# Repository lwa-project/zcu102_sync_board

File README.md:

ZCU102 Sync Board
=================

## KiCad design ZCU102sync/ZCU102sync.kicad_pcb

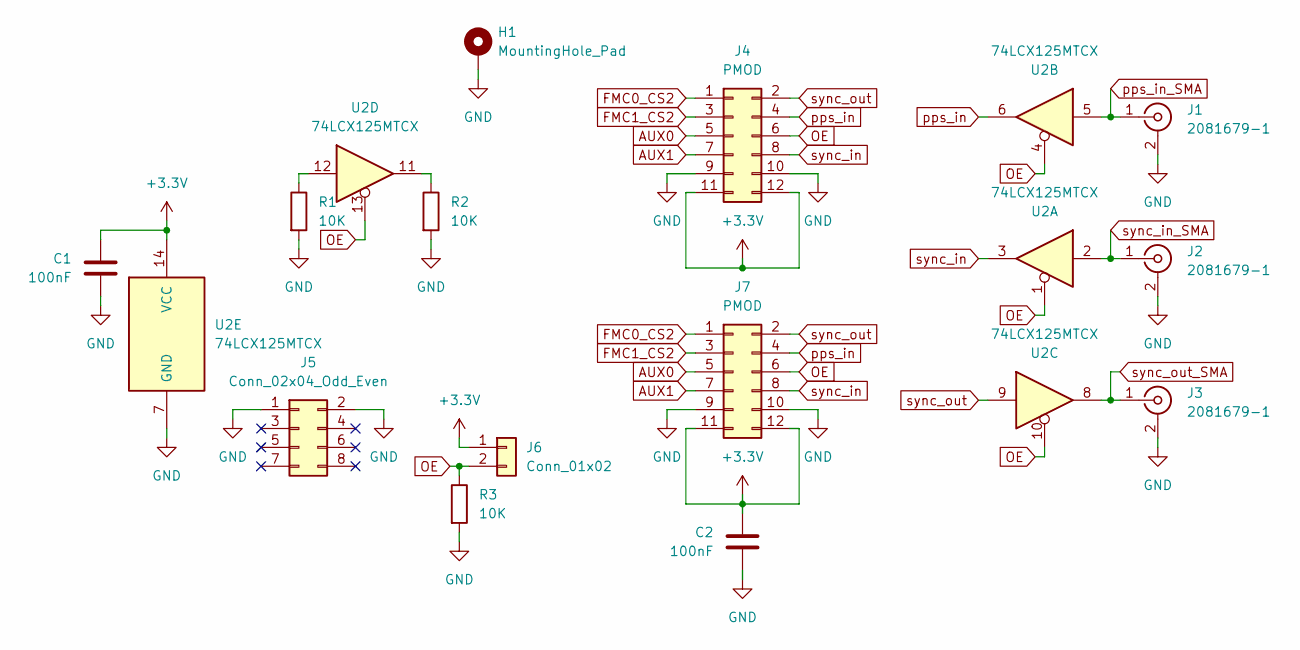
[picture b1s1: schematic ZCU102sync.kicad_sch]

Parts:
C1, C2: 100nF; C_1206_3216Metric_Pad1.33x1.80mm_HandSolder
H1: MountingHole_Pad; MountingHole_3.5mm_Pad_Via
J1, J2, J3: 2081679-1; SMA_Amphenol_132203-12_Horizontal
J4: PMOD; PinSocket_2x06_P2.54mm_Vertical
J5: Conn_02x04_Odd_Even; PinSocket_2x04_P2.54mm_Vertical
J6: Conn_01x02; PinHeader_2x01_P2.54mm_Vertical
J7: PMOD; PinHeader_2x06_P2.54mm_Vertical
R1, R2, R3: 10K; R_1206_3216Metric_Pad1.30x1.75mm_HandSolder
U2: 74LCX125MTCX; TSSOP-14_4.4x5mm_P0.65mm

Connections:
+3.3V: C1.1, C2.1, J4.11, J4.12, J6.1, J7.11, J7.12, U2.14 (VCC)
AUX0: J4.5, J7.5
AUX1: J4.7, J7.7
FMC0_CS2: J4.1, J7.1
FMC1_CS2: J4.3, J7.3
GND: C1.2, C2.2, H1.1, J1.2 (Ext), J2.2 (Ext), J3.2 (Ext), J4.9, J4.10, J5.1, J5.2, J7.9, J7.10, R1.2, R2.2, R3.2, U2.7 (GND)
unnamed: R1.1, U2.12
unnamed: R2.1, U2.11
OE: J4.6, J6.2, J7.6, R3.1, U2.1, U2.4, U2.10, U2.13
pps_in: J4.4, J7.4, U2.6
pps_in_SMA: J1.1 (In), U2.5
sync_in: J4.8, J7.8, U2.3
sync_in_SMA: J2.1 (In), U2.2
sync_out: J4.2, J7.2, U2.9
sync_out_SMA: J3.1 (In), U2.8

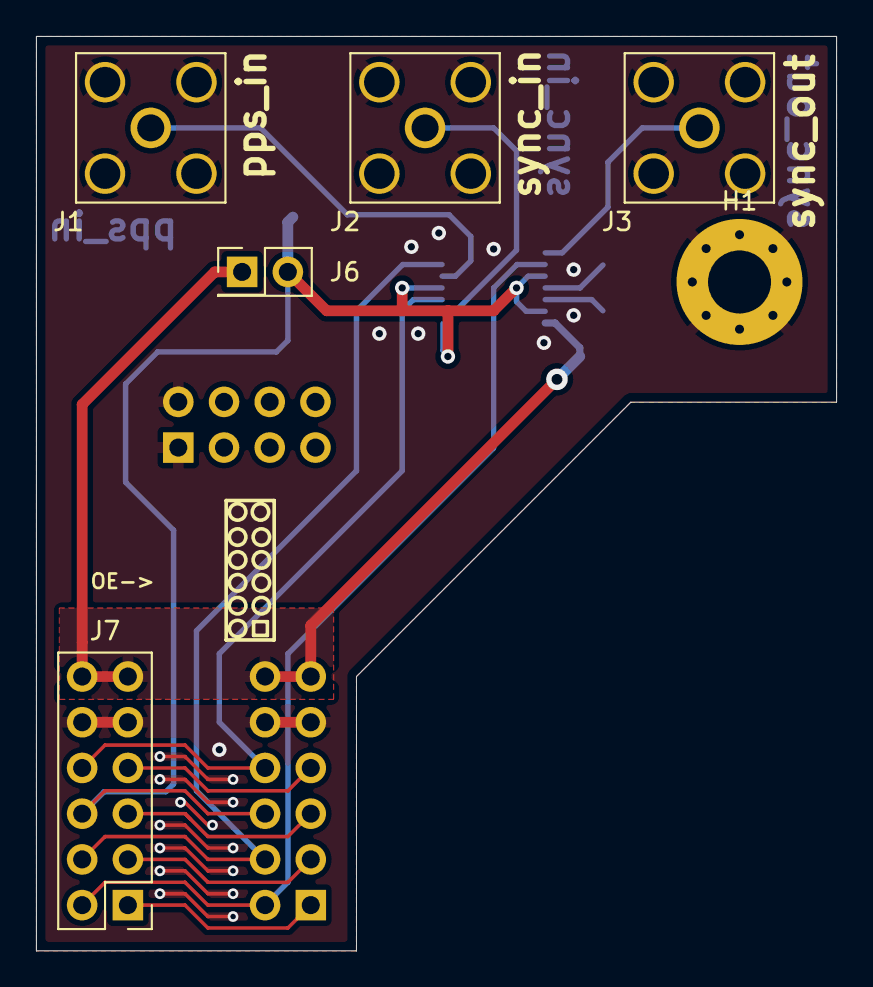
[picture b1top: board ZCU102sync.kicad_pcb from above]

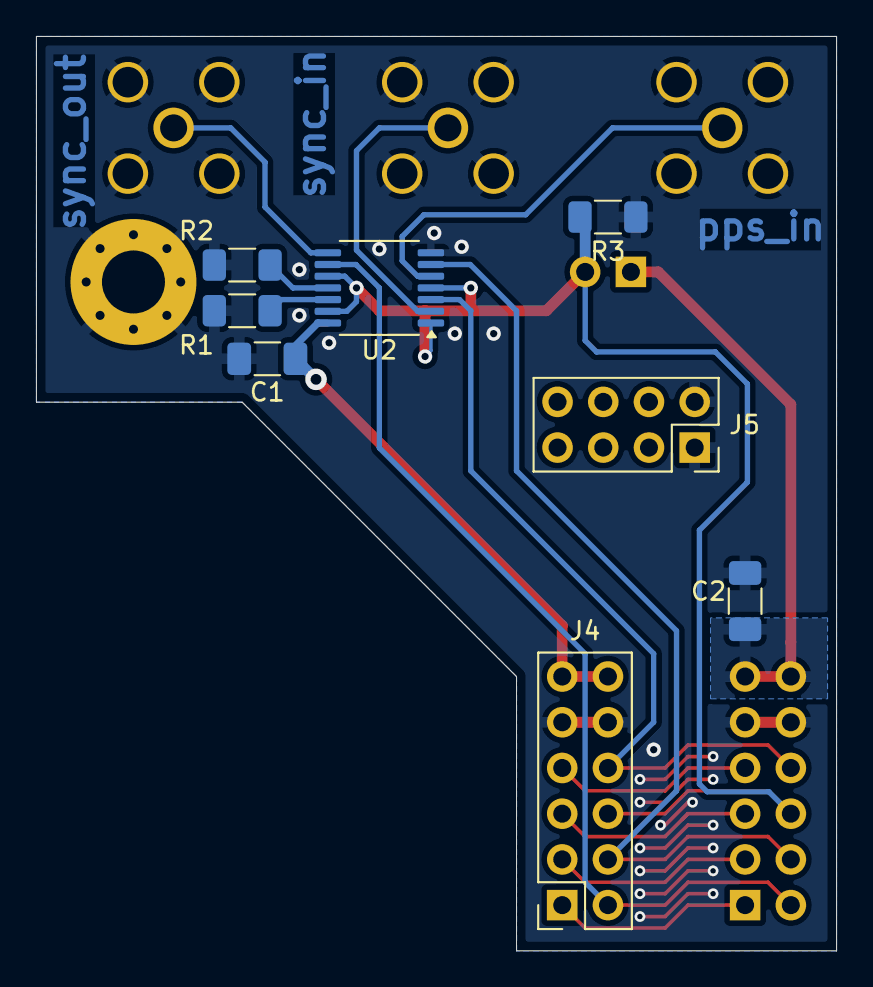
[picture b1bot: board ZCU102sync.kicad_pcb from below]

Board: 2 copper layers, 44.4 x 50.8 mm, 14 parts (8 on the bottom side), 15 nets.

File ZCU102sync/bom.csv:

Comment,Designator,Footprint,LCSC
"100nF","C1,C2","Capacitor_SMD:C_1206_3216Metric_Pad1.33x1.80mm_HandSolder","C93194"
"2081679-1","J1,J2,J3","Connector_Coaxial:SMA_Amphenol_132203-12_Horizontal","C5723204"
"PMOD","J4","Connector_PinSocket_2.54mm:PinSocket_2x06_P2.54mm_Vertical","C36191"
"Conn_02x04_Odd_Even","J5","Connector_PinSocket_2.54mm:PinSocket_2x04_P2.54mm_Vertical","C22373909"
"Conn_01x02","J6","Connector_PinHeader_2.54mm:PinHeader_2x01_P2.54mm_Vertical","C5383111"
"PMOD","J7","Connector_PinHeader_2.54mm:PinHeader_2x06_P2.54mm_Vertical","C36191"
"10K","R1,R2,R3","Resistor_SMD:R_1206_3216Metric_Pad1.30x1.75mm_HandSolder","C2907423"
"SN74LVC125","U2","Package_SO:TSSOP-14_4.4x5mm_P0.65mm","C7813"

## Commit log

2025-10-08 Add README.md.
2025-10-08 Add the files.
2025-10-08 It's KiCAD.
